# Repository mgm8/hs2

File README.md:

<h1 align="center">
    HS2
    <br>
</h1>

<h4 align="center">Analog guitar pedal based on Boss HM-2.</h4>

<p align="center">

</p>

<p align="center">
    <a href="#overview">Overview</a> •
    <a href="#license">License</a>
</p>

## Overview

This is an analog guitar pedal based on the Boss HM-2, using the schematics of the project "[The Swede](https://buildyourownclone.myshopify.com/products/the-swede)" as main reference.

## PCB

The Printed Circuit Board of version v1.0 of the project can be seen below:

This PCB was a courtesy of [PCBWay](https://www.pcbway.com/).

## Bill of Materials

| ID | Designator                            | Quantity | Description                               |
|----|---------------------------------------|----------|-------------------------------------------|
| 1  | C16                                   | 1        | Capacitor Film 100nF 25V                  |
| 2  | R16,R21                               | 2        | Resistor 68k 1/4W 1%                      |
| 3  | C23                                   | 1        | Capacitor Electrolytic 100uF 25V          |
| 4  | C8,C6,C2,C1,C21                       | 5        | Capacitor Film 47nF 25V                   |
| 5  | C11                                   | 1        | Capacitor Film 1nF 25V                    |
| 6  | Q1                                    | 1        | 2N5457                                    |
| 7  | R26,R35,R24,R10,R4,R14,R1,R36,R20,R19 | 10       | Resistor 10k 1/4W 1%                      |
| 8  | D8,D4,D1,D7,D2                        | 5        | 1N4148                                    |
| 9  | Q3                                    | 1        | 2N3906                                    |
| 10 | D5,D6                                 | 2        | 1N34A, 1N60, D9E, etc. (Germanium Diodes) |
| 11 | R23,R22                               | 2        | Resistor 3k3 1/4W 1%                      |
| 12 | C24,C5,C20                            | 3        | Capacitor Electrolytic 10uF 25V           |
| 13 | R7                                    | 1        | Resistor 22R 1/4W 1%                      |
| 14 | R2                                    | 1        | Resistor 1M 1/4W 1%                       |
| 15 | C12,C10,C22                           | 3        | Capacitor Electrolytic 1uF 25V            |
| 16 | R30,R34,R38,R32                       | 4        | Resistor 330R 1/4W 1%                     |
| 17 | R12,R28,R29,R33,R5                    | 5        | Resistor 100k 1/4W 1%                     |
| 18 | R18                                   | 1        | Resistor 220k 1/4W 1%                     |
| 19 | C19                                   | 1        | Capacitor Film 4.7nF 25V                  |
| 20 | U2,U3,U1                              | 3        | M5218L                                    |
| 21 | C4                                    | 1        | Capacitor Electrolytic 47uF 25V           |
| 22 | R27,R9                                | 2        | Resistor 1k 1/4W 1%                       |
| 23 | D3                                    | 1        | 1N4001                                    |
| 24 | R13,R6,R25                            | 3        | Resistor 470k 1/4W 1%                     |
| 25 | R17                                   | 1        | Resistor 47k 1/4W 1%                      |
| 26 | VR1                                   | 1        | Potentiometer Anti-Log 250k               |
| 27 | R31                                   | 1        | Resistor 82k 1/4W 1%                      |
| 28 | C13                                   | 1        | Capacitor Ceramic 470pF 25V               |
| 29 | C7,C3,C9                              | 3        | Capacitor Ceramic 100pF 25V               |
| 30 | R8                                    | 1        | Resistor 150R 1/4W 1%                     |
| 31 | VR3,VR2                               | 2        | Potentiometer Linear 50k                  |
| 32 | R11,R3                                | 2        | Resistor 22k 1/4W 1%                      |
| 33 | C17                                   | 1        | Capacitor Film 68nF 25V                   |
| 34 | VR4                                   | 1        | Potentiometer Log 10k                     |
| 35 | C14                                   | 1        | Capacitor Electrolytic 1.5uF 25V          |
| 36 | C18                                   | 1        | Capacitor Film 6.8nF 25V                  |
| 37 | R15                                   | 1        | Resistor 120R 1/4W 1%                     |
| 38 | Q2,Q4                                 | 2        | 2N3904                                    |
| 39 | C15                                   | 1        | Capacitor Film 150nF 25V                  |

## License

This project is licensed under CERN Open Hardware License, version 2.

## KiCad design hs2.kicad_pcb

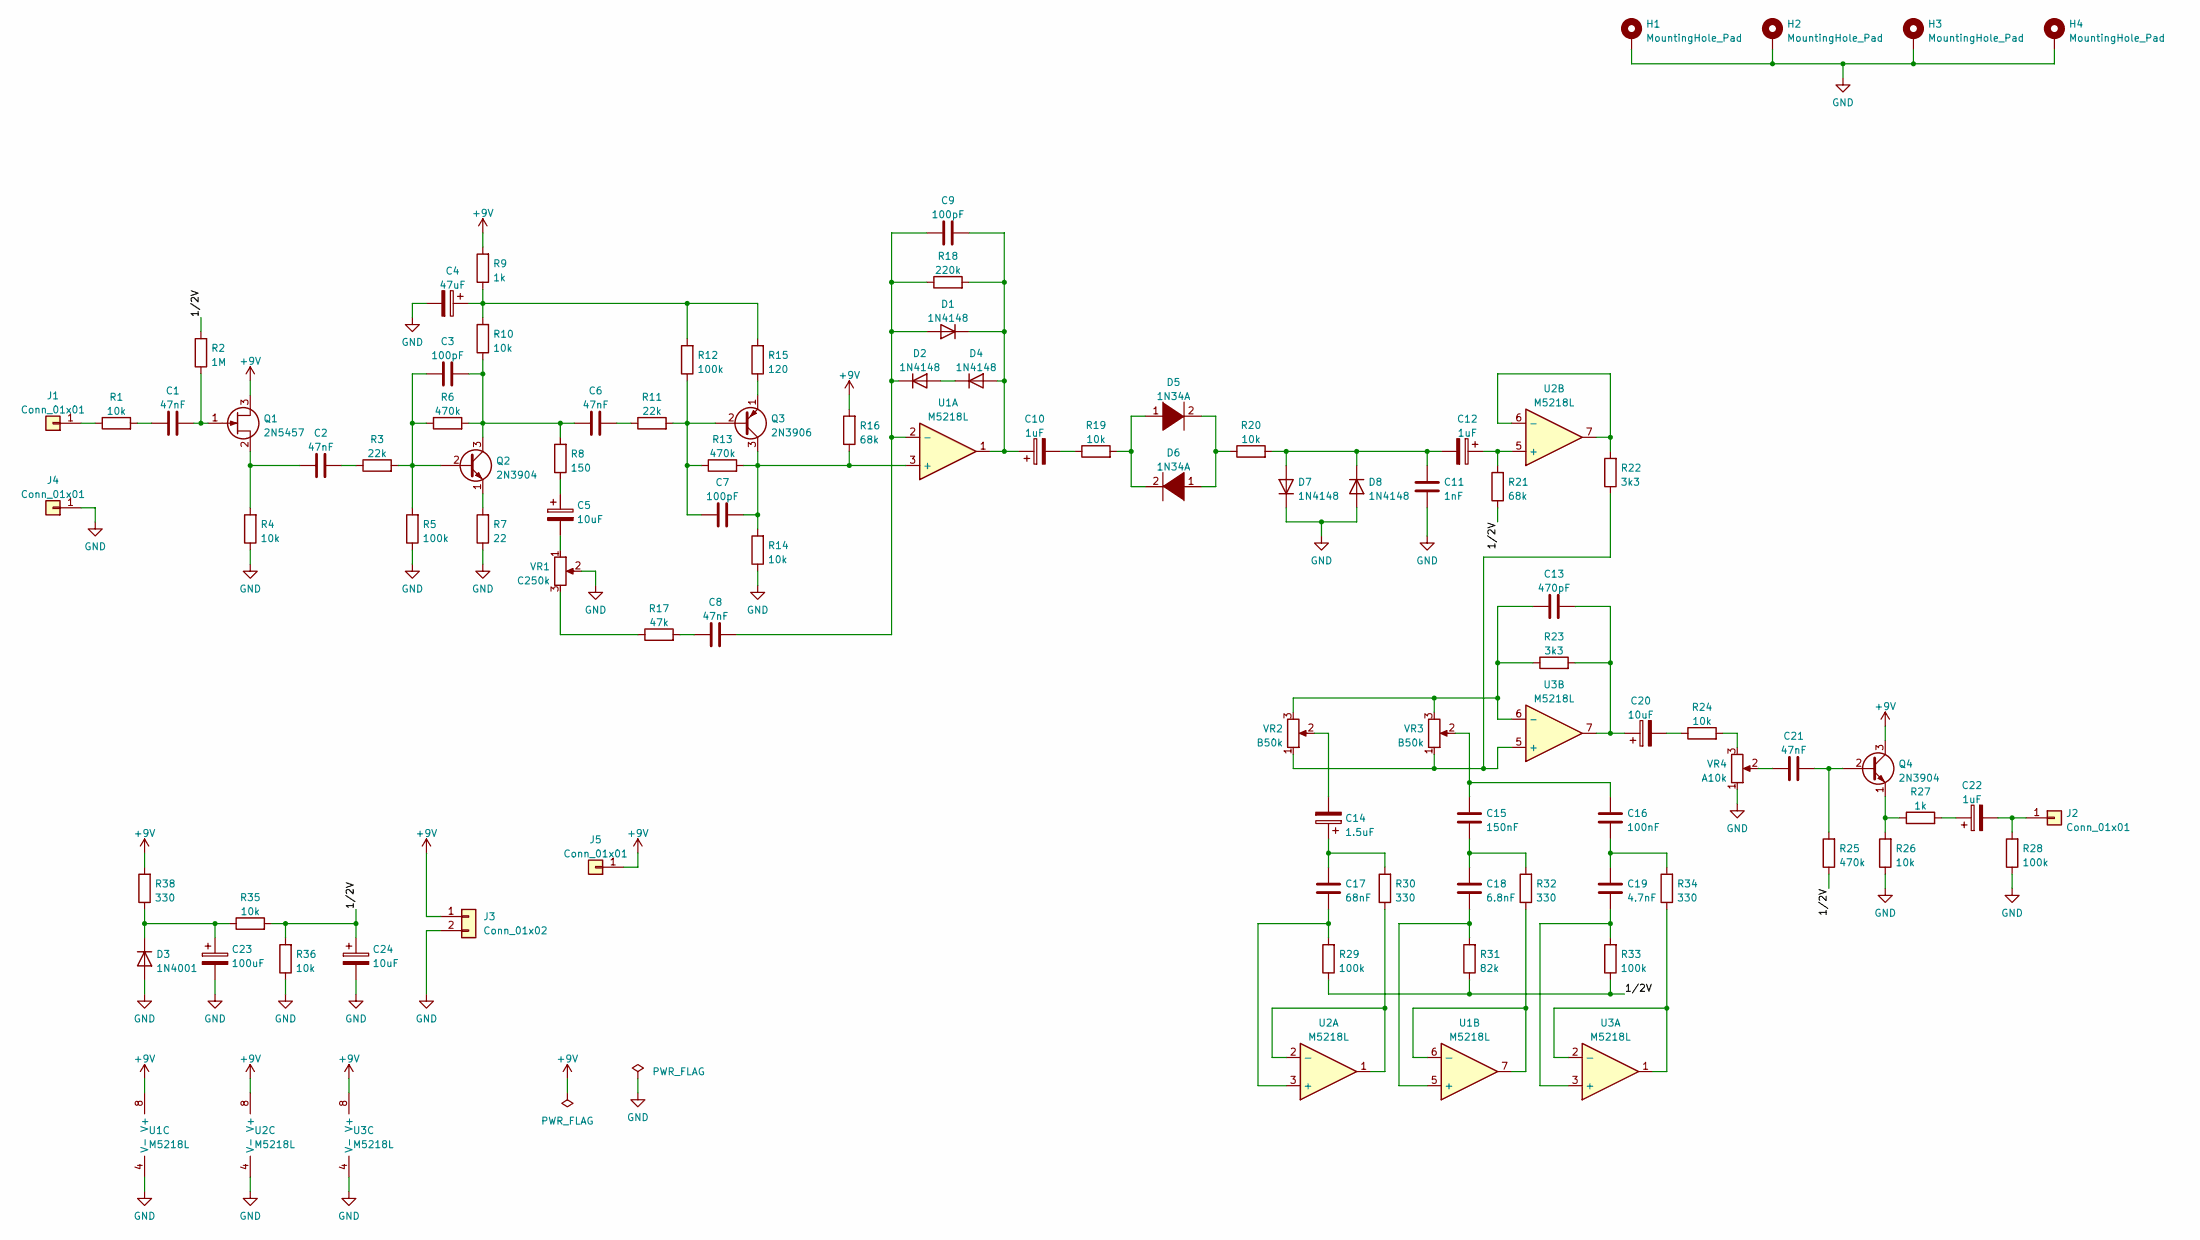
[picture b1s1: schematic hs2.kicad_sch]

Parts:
C1, C2, C6, C8, C21: 47nF; C_Disc_D4.3mm_W1.9mm_P5.00mm
C3, C7, C9: 100pF; C_Disc_D4.3mm_W1.9mm_P5.00mm
C4: 47uF; CP_Radial_D5.0mm_P2.50mm
C5, C20, C24: 10uF; CP_Radial_D5.0mm_P2.50mm
C10, C12, C22: 1uF; CP_Radial_D5.0mm_P2.50mm
C11: 1nF; CP_Radial_D5.0mm_P2.50mm
C13: 470pF; C_Disc_D4.3mm_W1.9mm_P5.00mm
C14: 1.5uF; CP_Radial_D5.0mm_P2.50mm
C15: 150nF; C_Disc_D4.3mm_W1.9mm_P5.00mm
C16: 100nF; C_Disc_D4.3mm_W1.9mm_P5.00mm
C17: 68nF; C_Disc_D4.3mm_W1.9mm_P5.00mm
C18: 6.8nF; C_Disc_D4.3mm_W1.9mm_P5.00mm
C19: 4.7nF; C_Disc_D4.3mm_W1.9mm_P5.00mm
C23: 100uF; CP_Radial_D5.0mm_P2.50mm
D1, D2, D4, D7, D8: 1N4148; D_DO-35_SOD27_P7.62mm_Horizontal
D3: 1N4001; D_DO-41_SOD81_P10.16mm_Horizontal
D5, D6: 1N34A; D_DO-41_SOD81_P10.16mm_Horizontal
H1, H2, H3, H4: MountingHole_Pad; MountingHole_3.2mm_M3_Pad_TopBottom
J1, J2, J4, J5: Conn_01x01; PinHeader_1x01_P2.54mm_Vertical
J3: Conn_01x02; PinHeader_1x02_P2.54mm_Vertical
Q1: 2N5457; TO-92_Inline
Q2, Q4: 2N3904; TO-92_Inline
Q3: 2N3906; TO-92_Inline
R1, R4, R10, R14, R19, R20, R24, R26, R35, R36: 10k; R_Axial_DIN0207_L6.3mm_D2.5mm_P10.16mm_Horizontal
R2: 1M; R_Axial_DIN0207_L6.3mm_D2.5mm_P10.16mm_Horizontal
R3, R11: 22k; R_Axial_DIN0207_L6.3mm_D2.5mm_P10.16mm_Horizontal
R5, R12, R28, R29, R33: 100k; R_Axial_DIN0207_L6.3mm_D2.5mm_P10.16mm_Horizontal
R6, R13, R25: 470k; R_Axial_DIN0207_L6.3mm_D2.5mm_P10.16mm_Horizontal
R7: 22; R_Axial_DIN0207_L6.3mm_D2.5mm_P10.16mm_Horizontal
R8: 150; R_Axial_DIN0207_L6.3mm_D2.5mm_P10.16mm_Horizontal
R9, R27: 1k; R_Axial_DIN0207_L6.3mm_D2.5mm_P10.16mm_Horizontal
R15: 120; R_Axial_DIN0207_L6.3mm_D2.5mm_P10.16mm_Horizontal
R16, R21: 68k; R_Axial_DIN0207_L6.3mm_D2.5mm_P10.16mm_Horizontal
R17: 47k; R_Axial_DIN0207_L6.3mm_D2.5mm_P10.16mm_Horizontal
R18: 220k; R_Axial_DIN0207_L6.3mm_D2.5mm_P10.16mm_Horizontal
R22, R23: 3k3; R_Axial_DIN0207_L6.3mm_D2.5mm_P10.16mm_Horizontal
R30, R32, R34, R38: 330; R_Axial_DIN0207_L6.3mm_D2.5mm_P10.16mm_Horizontal
R31: 82k; R_Axial_DIN0207_L6.3mm_D2.5mm_P10.16mm_Horizontal
U1, U2, U3: M5218L; SIP-8_19x3mm_P2.54mm
VR1: C250k; TerminalBlock_bornier-3_P5.08mm
VR2, VR3: B50k; TerminalBlock_bornier-3_P5.08mm
VR4: A10k; TerminalBlock_bornier-3_P5.08mm

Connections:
+9V: J3.1, J5.1, Q1.3 (D), Q4.3 (C), R9.2, R16.2, R38.2, U1.8 (V+), U2.8 (V+), U3.8 (V+)
/1/2V: C24.1, R2.2, R21.1, R25.1, R29.1, R31.1, R33.1, R35.2, R36.2
GND: C4.2, C11.2, C23.2, C24.2, D3.2 (A), D7.1 (K), D8.2 (A), H1.1, H2.1, H3.1, H4.1, J3.2, J4.1, R4.1, R5.1, R7.1, R14.1, R26.1, R28.1, R36.1, U1.4 (V-), U2.4 (V-), U3.4 (V-), VR1.2, VR4.1
unnamed: C1.1, R1.2
unnamed: C1.2, Q1.1 (G), R2.1
unnamed: C2.1, Q1.2 (S), R4.2
unnamed: C2.2, R3.1
unnamed: C3.1, Q2.2 (B), R3.2, R5.2, R6.1
unnamed: C3.2, C6.1, Q2.3 (C), R6.2, R8.2, R10.1
unnamed: C4.1, R9.1, R10.2, R12.2, R15.2
unnamed: C5.1, R8.1
unnamed: C5.2, VR1.1
unnamed: C6.2, R11.1
unnamed: C7.1, Q3.2 (B), R11.2, R12.1, R13.1
unnamed: C7.2, Q3.3 (C), R13.2, R14.2, R16.1, U1.3 (+)
unnamed: C8.1, R17.2
unnamed: C8.2, C9.1, D1.2 (A), D2.1 (K), R18.1, U1.2 (-)
unnamed: C9.2, C10.1, D1.1 (K), D4.2 (A), R18.2, U1.1
unnamed: C10.2, R19.1
unnamed: C11.1, C12.2, D7.2 (A), D8.1 (K), R20.2
unnamed: C12.1, R21.2, U2.5 (+)
unnamed: C13.1, R23.1, U3.6 (-), VR2.3, VR3.3
unnamed: C13.2, C20.1, R23.2, U3.7
unnamed: C14.1, C17.1, R30.2
unnamed: C14.2, VR2.2
unnamed: C15.1, C16.1, VR3.2
unnamed: C15.2, C18.1, R32.2
unnamed: C16.2, C19.1, R34.2
unnamed: C17.2, R29.2, U2.3 (+)
unnamed: C18.2, R31.2, U1.5 (+)
unnamed: C19.2, R33.2, U3.3 (+)
unnamed: C20.2, R24.1
unnamed: C21.1, VR4.2
unnamed: C21.2, Q4.2 (B), R25.2
unnamed: C22.1, R27.2
unnamed: C22.2, J2.1, R28.2
unnamed: C23.1, D3.1 (K), R35.1, R38.1
unnamed: D2.2 (A), D4.1 (K)
unnamed: D5.1 (K), D6.2 (A), R19.2
unnamed: D5.2 (A), D6.1 (K), R20.1
unnamed: J1.1, R1.1
unnamed: Q2.1 (E), R7.2
unnamed: Q3.1 (E), R15.1
unnamed: Q4.1 (E), R26.2, R27.1
unnamed: R17.1, VR1.3
unnamed: R22.1, U3.5 (+), VR2.1, VR3.1
unnamed: R22.2, U2.6 (-), U2.7
unnamed: R24.2, VR4.3
unnamed: R30.1, U2.1, U2.2 (-)
unnamed: R32.1, U1.6 (-), U1.7
unnamed: R34.1, U3.1, U3.2 (-)

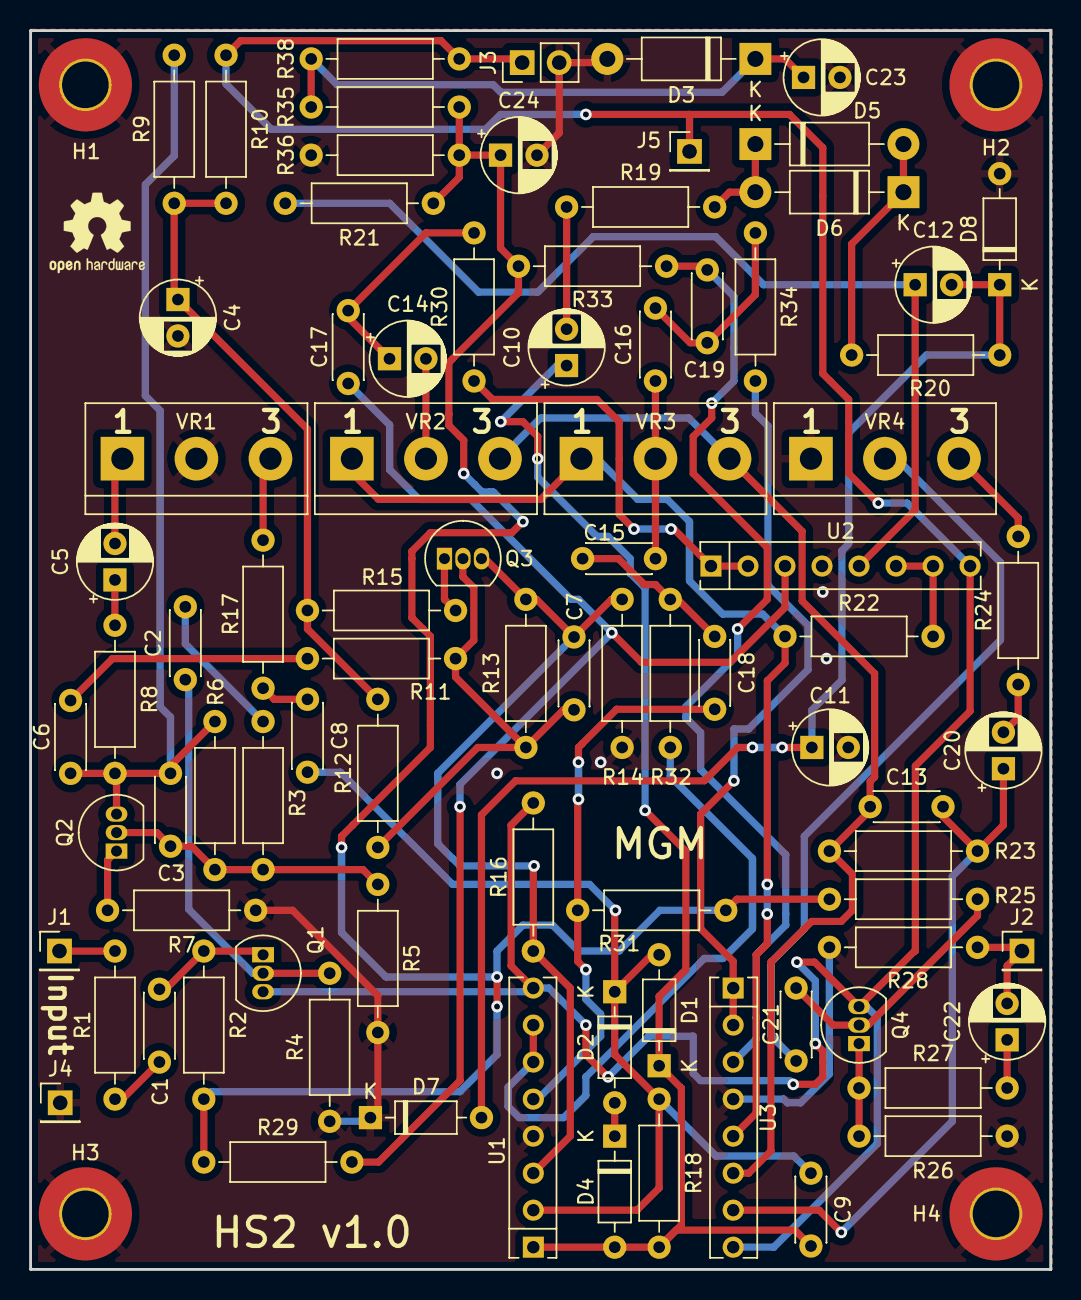
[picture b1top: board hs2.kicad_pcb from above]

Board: 2 copper layers, 70.0 x 85.0 mm, 89 parts (0 on the bottom side), 51 nets.

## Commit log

2022-07-22 Creating the project in KiCad
2022-07-22 schematics: Placing symbols
2022-07-24 Renaming the project
2022-07-24 Defining the project license as CERN OHL v2
2022-08-02 schematics: Drawing the circuit
2022-08-09 schematics: First version of the schematics
2022-08-11 Updating the designators and initial footprint assignment
2023-04-22 layout: Components placement
2023-04-22 Adding kibot workflow
2023-04-22 layout: Routing finished
2023-04-22 layout: Adding logos and text
2023-04-22 layout: Fixing the position of the labels
2023-04-22 Updating the main README and adding a 3D render of the PCB
2023-04-23 Updating the main README
2023-04-23 Fixing kibot workflow script
2023-04-23 schematics: Fixing ERC errors
2023-04-24 layout: Fixing DRC warnings
2023-04-24 Minor improvements
2023-04-24 Disabling the image renderization in the kibot workflow script
2023-04-29 Adding the BOM to the README file
2023-04-29 Minor fixes in the schematics
2023-04-29 docs: Updating the 3D render images
2023-06-24 Adding pictures of the PCB and updating the main README
2023-06-28 Updating the main README with a section about the PCB prototype

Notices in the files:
README.md:
License: CERN OHL 2
